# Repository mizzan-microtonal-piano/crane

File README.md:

# crane
Controller board for the Mizzan Microtonal Piano

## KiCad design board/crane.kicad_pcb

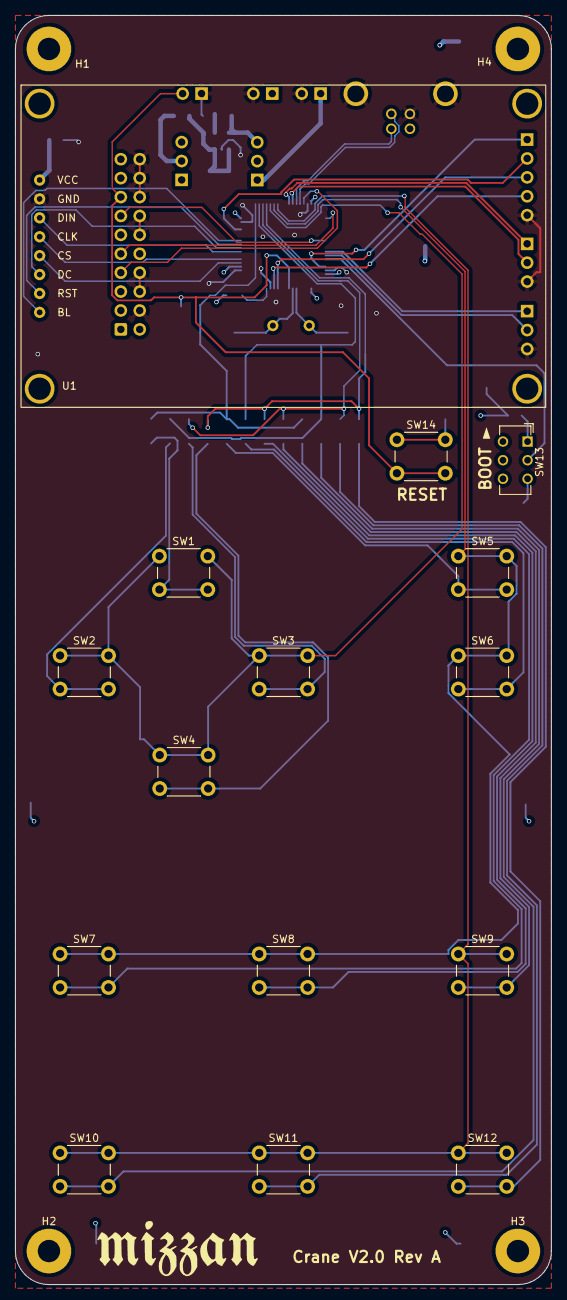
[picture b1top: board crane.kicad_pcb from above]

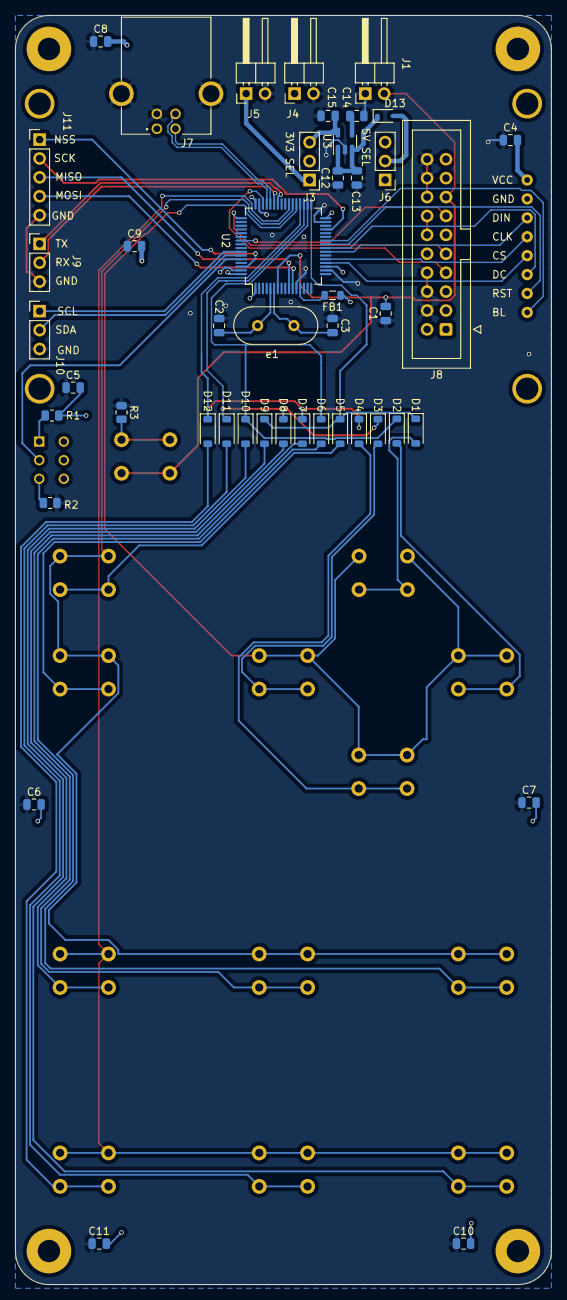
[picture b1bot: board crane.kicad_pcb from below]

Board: 4 copper layers, 72.0 x 170.5 mm, 64 parts (45 on the bottom side), 55 nets.

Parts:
C1, C6, C7, C8, C9, C13: 100nF; C_0805_2012Metric
C2, C3: 20pF; C_0805_2012Metric
C4, C5: 10nF; C_0805_2012Metric
C10, C15: 1uF; C_0805_2012Metric
C11: 10uF; C_0805_2012Metric
C12: 1uF_X5R; C_0805_2012Metric
C14: 10nF_X7R; C_0805_2012Metric
D1, D2, D3, D4, D5, D6, D7, D8, D9, D10, D11, D12: D; D_SOD-123
D13: BAT60AE6327HTSA1; D_SOD-323
FB1: HZ0805E601R-10; L_0805_2012Metric
H1, H2, H3, H4: MountingHole; MountingHole_3mm_Pad
J1, J4, J5: Conn_01x02_Male; PinHeader_1x02_P2.54mm_Horizontal
J3, J6: Conn_01x03_Male; PinHeader_1x03_P2.54mm_Vertical
J7: 292304-1; TE_292304-1
J8: Conn_ARM_JTAG_SWD_20; IDC-Header_2x10_P2.54mm_Vertical
J9, J10: Conn_01x03; PinHeader_1x03_P2.54mm_Vertical
J11: Conn_01x05; PinHeader_1x05_P2.54mm_Vertical
R1, R2: 10K; R_0805_2012Metric
R3: 100; R_0805_2012Metric
SW1, SW2, SW3, SW4, SW5, SW6, SW7, SW8, SW9, SW10, SW11, SW12, SW14: SW_Push; SW_PUSH_6mm_H9.5mm
SW13: SW_Push_DPDT; SW_CuK_JS202011CQN_DPDT_Straight
U1: Waveshare_LCD_Module_2.4in; Waveshare_LCD_Module_2_4in
U2: STM32L476RGT6; LQFP-64_10x10mm_P0.5mm
U3: LD3985M33R_SOT23; SOT-23-5
e1: 9B-16.000MAAE-B; Crystal_HC49-U_Vertical

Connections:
3.3V_EXT: J3.1, J5.1
3.3V_REG: C15.2, J3.3, U3.5 (VOUT)
5V_EXT: J4.1, J6.1
+3V3: C4.2, C5.2, C6.2, C7.2, C8.2, C9.2, C10.2, C11.2, FB1.1, J3.2, J8.1 (VTREF), R1.1, U1.1 (VCC), U2.1 (VBAT), U2.19 (VDD), U2.32 (VDD), U2.48 (VDDUSB), U2.64 (VDD)
+5V: D13.2 (A), J6.2
BOOT0: SW13.2 (B), U2.60 (PH3)
GND: C1.1, C2.1, C3.1, C4.1, C5.1, C6.1, C7.1, C8.1, C9.1, C10.1, C11.1, C12.1, C13.1, C14.1, C15.1, J1.1, J4.2, J5.2, J7.0 (SHEILD), J7.4 (GND), J8.4 (GND), J8.6 (GND), J8.8 (GND), J8.10 (GND), J8.12 (GND), J8.14 (GND), J8.16 (GND), J8.18 (GND), J8.20 (GND), J9.3, J10.3, J11.5, R2.2, R3.1, U1.2 (GND), U2.12 (VSSA), U2.18 (VSS), U2.31 (VSS), U2.47 (VSS), U2.63 (VSS), U3.2 (GND)
I2C_SCL: J10.1, U2.58 (PB6)
I2C_SDA: J10.2, U2.59 (PB7)
JTCK_SWCLK: J8.9 (TCK/SWDCLK), U2.49 (PA14)
JTDO_SWO: J8.13 (TDO/SWO), U2.55 (PB3)
JTMS_SWDIO: J8.7 (TMS/SWDIO), U2.46 (PA13)
LCD_BL: U1.8 (BL), U2.26 (PB0)
LCD_CLK: U1.4 (CLK), U2.21 (PA5)
LCD_CS: U1.5 (CS), U2.20 (PA4)
LCD_DC: U1.6 (DS), U2.24 (PC4)
LCD_DIN: U1.3 (DIN), U2.23 (PA7)
LCD_RST: U1.7 (RST), U2.25 (PC5)
NRST: C1.2, J1.2, J8.15 (~SRST), SW14.2, U2.7 (NRST)
unnamed: D1.2 (A), SW1.2
unnamed: D2.2 (A), SW2.2
unnamed: D3.2 (A), SW3.2
unnamed: D4.2 (A), SW4.2
unnamed: D5.2 (A), SW5.2
unnamed: D6.2 (A), SW6.2
unnamed: D7.2 (A), SW7.2
unnamed: D8.2 (A), SW8.2
unnamed: D9.2 (A), SW9.2
unnamed: D10.2 (A), SW10.2
unnamed: D11.2 (A), SW11.2
unnamed: D12.2 (A), SW12.2
unnamed: C12.2, C13.2, D13.1 (K), U3.1 (VIN), U3.3 (INH)
unnamed: R1.2, SW13.1 (A)
unnamed: R2.1, SW13.3 (C)
unnamed: R3.2, SW14.1
unnamed: C2.2, U2.5 (PH0), e1.1
unnamed: C3.2, U2.6 (PH1), e1.2
unnamed: FB1.2, U2.13 (VDDA)
unnamed: C14.2, U3.4 (BYP)
SPI_MISO: J11.3, U2.10 (PC2)
SPI_MOSI: J11.4, U2.11 (PC3)
SPI_NSS: J11.1, U2.62 (PB9)
SPI_SCK: J11.2, U2.29 (PB10)
SW_C0: SW1.1, SW2.1, SW3.1, SW4.1, U2.37 (PC6)
SW_C1: SW5.1, SW6.1, SW7.1, SW8.1, U2.38 (PC7)
SW_C2: SW9.1, SW10.1, SW11.1, SW12.1, U2.39 (PC8)
SW_R0: D1.1 (K), D5.1 (K), D9.1 (K), U2.33 (PB12)
SW_R1: D2.1 (K), D6.1 (K), D10.1 (K), U2.34 (PB13)
SW_R2: D3.1 (K), D8.1 (K), D11.1 (K), U2.35 (PB14)
SW_R3: D4.1 (K), D7.1 (K), D12.1 (K), U2.36 (PB15)
USART_RX: J9.2, U2.43 (PA10)
USART_TX: J9.1, U2.42 (PA9)
USB_OTG_FS_D+: J7.3 (D+), U2.45 (PA12)
USB_OTG_FS_D-: J7.2 (D-), U2.44 (PA11)
USB_VBUS: J6.3, J7.1 (VBUS)

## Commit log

2022-10-23 added project files and folders
2022-11-02 Completed routing
2022-11-02 Added Gerber Files in folder gerber/
2022-11-02 Added Mizzan Logo
2022-11-02 Removed layer alignmetn target
2022-11-02 updated gerber files
2022-11-02 Added image to README.md
2022-12-15 tested LCD, button scan and serial output
2023-04-11 0.0.0
2023-04-11 0.0.1
2023-04-11 0.0.2
    fixing the list of instruments for prototype 2
2023-04-11 0.0.3
    preparing crane for prototype 2
2023-05-09 updated to Crane V2 Rev A
2023-05-19 diode footprint change drom 0805 (2012) to SOD123
2023-05-28 removed software folder
2023-05-28 places existing software files under the folder named software
2023-05-28 modified software for Board V2 Rev A. Needs testing
2023-05-28 changed Serial to SerialUSB in OneButton_Clicks.h
2023-05-30 fixed button order and tested
2023-05-31 removed debug condition for use of button 0 and button 1
2023-05-31 debug condition for printing button 1 debug added
2023-06-19 updated image in Resources for readme
2024-08-25 added 3D object
